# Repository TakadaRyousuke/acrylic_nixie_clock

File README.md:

# acrylic_nixie_clock
アクリル板を用いた疑似ニキシー時計のRepository。　回路データ、3DCADデータ、プログラムなど全部

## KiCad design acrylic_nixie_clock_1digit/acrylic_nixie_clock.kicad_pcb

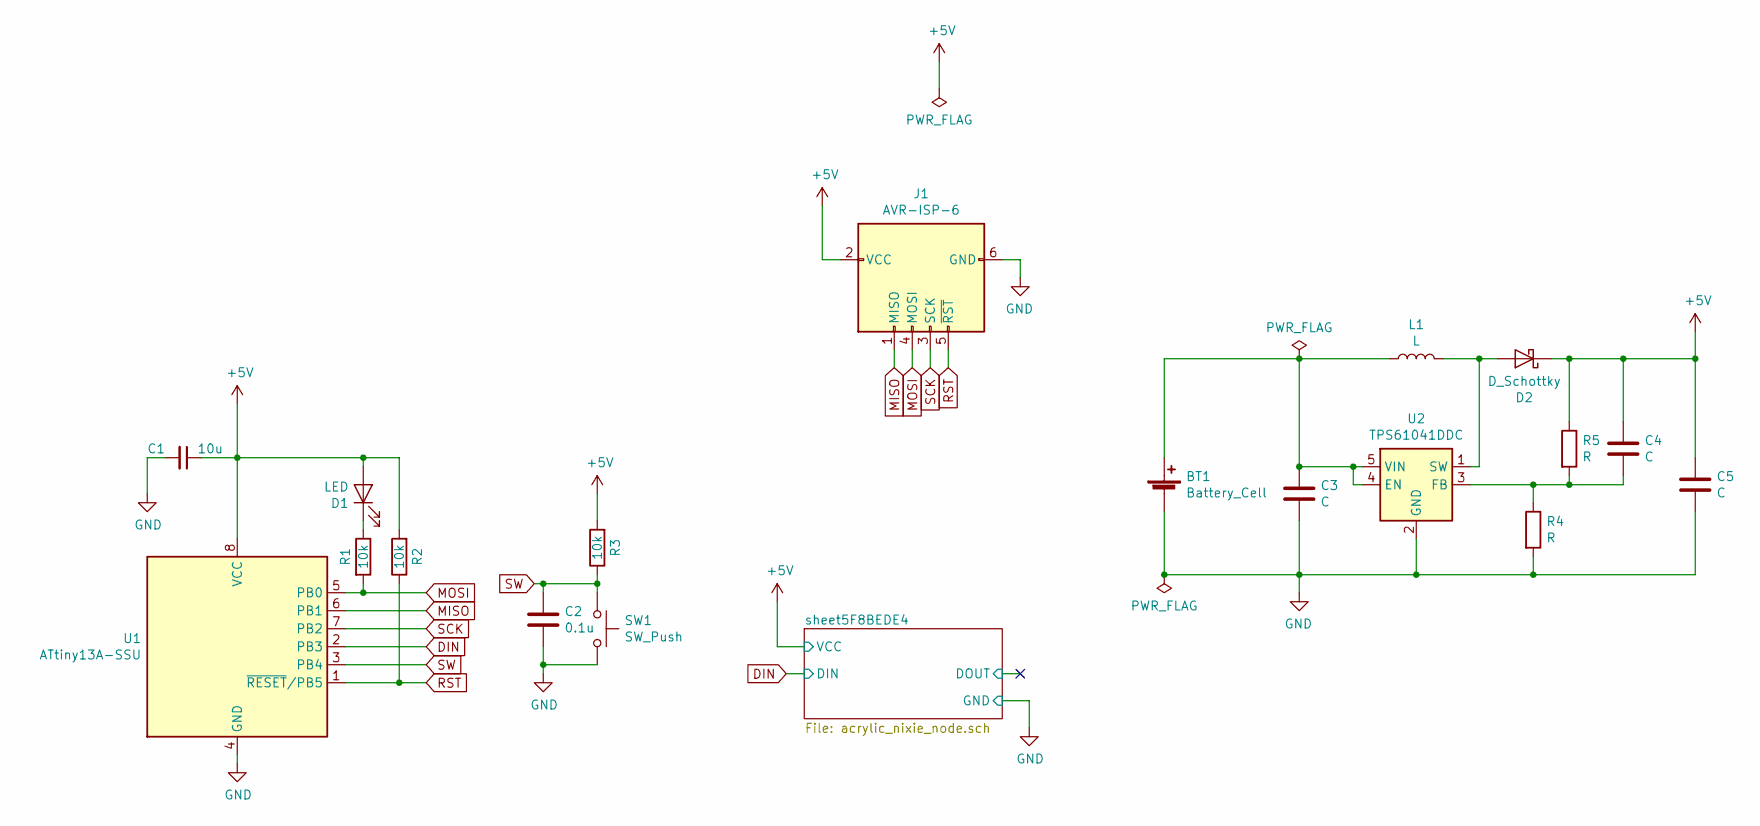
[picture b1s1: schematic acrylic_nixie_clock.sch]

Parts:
BT1: Battery_Cell; BatteryHolder_Keystone_1058_1x2032
C1: 10u; C_0603_1608Metric; LCSC C19702
C2: 0.1u; C_0603_1608Metric; LCSC C14858
C3, C4, C5: C; C_0603_1608Metric
D1: LED; LED_0603_1608Metric
D2: D_Schottky; D_SOD-123
J1: AVR-ISP-6; ISP-6
L1: L; L_0603_1608Metric
R1, R2, R3: 10k; R_0603_1608Metric_Pad1.05x0.95mm_HandSolder; LCSC C25804
R4, R5: R; R_0603_1608Metric_Pad1.05x0.95mm_HandSolder
SW1: SW_Push; SW_SPST_TL3342; LCSC C318884
U1: ATtiny13A-SSU; SOIC-8_3.9x4.9mm_P1.27mm
U2: TPS61041DDC; SOT-23-5

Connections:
+5V: C1.1, C4.1, C5.1, D1.2 (A), D2.1 (K), J1.2 (VCC), R2.2, R3.2, R5.1, U1.8 (VCC); also elsewhere on the board
DIN: U1.2 (PB3); also elsewhere on the board
GND: BT1.2 (-), C1.2, C2.2, C3.2, C5.2, J1.6 (GND), R4.2, SW1.2, U1.4 (GND), U2.2 (GND); also elsewhere on the board
MISO: J1.1 (MISO), U1.6 (PB1)
MOSI: J1.4 (MOSI), R1.2, U1.5 (PB0)
unnamed: BT1.1 (+), C3.1, L1.1, U2.4 (EN), U2.5 (VIN)
unnamed: C4.2, R4.1, R5.2, U2.3 (FB)
unnamed: D1.1 (K), R1.1
unnamed: D2.2 (A), L1.2, U2.1 (SW)
RST: J1.5 (~RST), R2.1, U1.1 (~RESET~/PB5)
SCK: J1.3 (SCK), U1.7 (PB2)
SW: C2.1, R3.1, SW1.1, U1.3 (PB4)

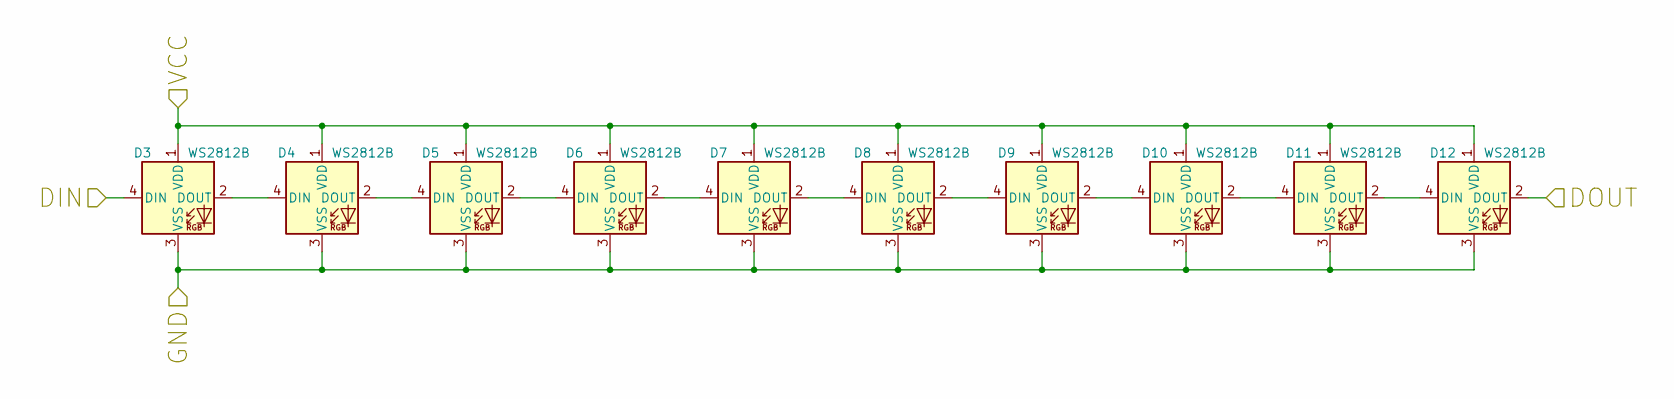
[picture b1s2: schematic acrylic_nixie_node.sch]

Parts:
D3, D4, D5, D6, D7, D8, D9, D10, D11, D12: WS2812B; LED_WS2812B_PLCC4_5.0x5.0mm_P3.2mm; LCSC C114586

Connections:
+5V: D3.1 (VDD), D4.1 (VDD), D5.1 (VDD), D6.1 (VDD), D7.1 (VDD), D8.1 (VDD), D9.1 (VDD), D10.1 (VDD), D11.1 (VDD), D12.1 (VDD); also elsewhere on the board
/sheet5F8BEDE4/DOUT: D12.2 (DOUT)
DIN: D3.4 (DIN); also elsewhere on the board
GND: D3.3 (VSS), D4.3 (VSS), D5.3 (VSS), D6.3 (VSS), D7.3 (VSS), D8.3 (VSS), D9.3 (VSS), D10.3 (VSS), D11.3 (VSS), D12.3 (VSS); also elsewhere on the board
unnamed: D3.2 (DOUT), D4.4 (DIN)
unnamed: D4.2 (DOUT), D5.4 (DIN)
unnamed: D5.2 (DOUT), D6.4 (DIN)
unnamed: D6.2 (DOUT), D7.4 (DIN)
unnamed: D7.2 (DOUT), D8.4 (DIN)
unnamed: D8.2 (DOUT), D9.4 (DIN)
unnamed: D10.2 (DOUT), D11.4 (DIN)
unnamed: D9.2 (DOUT), D10.4 (DIN)
unnamed: D11.2 (DOUT), D12.4 (DIN)

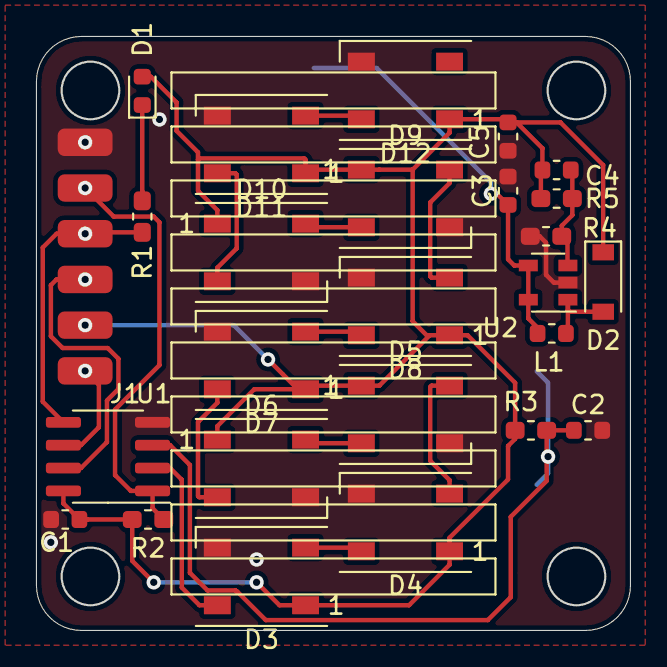
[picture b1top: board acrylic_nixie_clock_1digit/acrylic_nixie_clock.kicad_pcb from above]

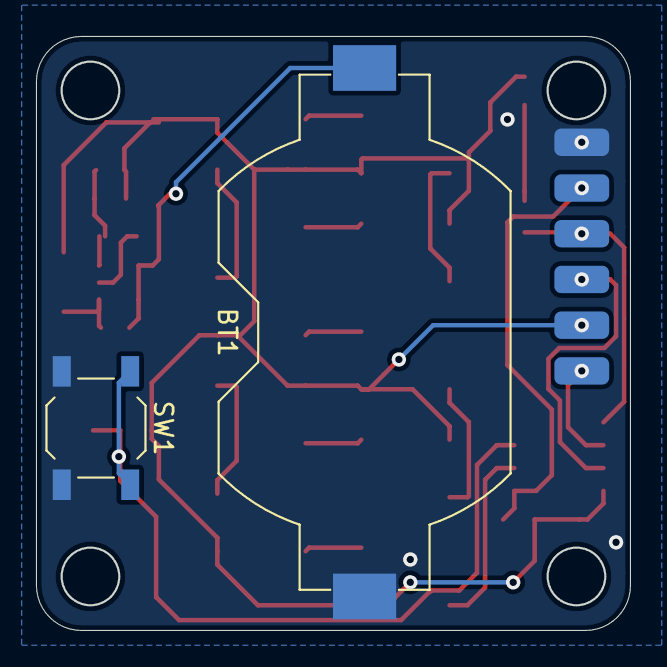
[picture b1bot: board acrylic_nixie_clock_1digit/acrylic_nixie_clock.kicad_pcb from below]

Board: 2 copper layers, 33.0 x 33.0 mm, 28 parts (2 on the bottom side), 21 nets.

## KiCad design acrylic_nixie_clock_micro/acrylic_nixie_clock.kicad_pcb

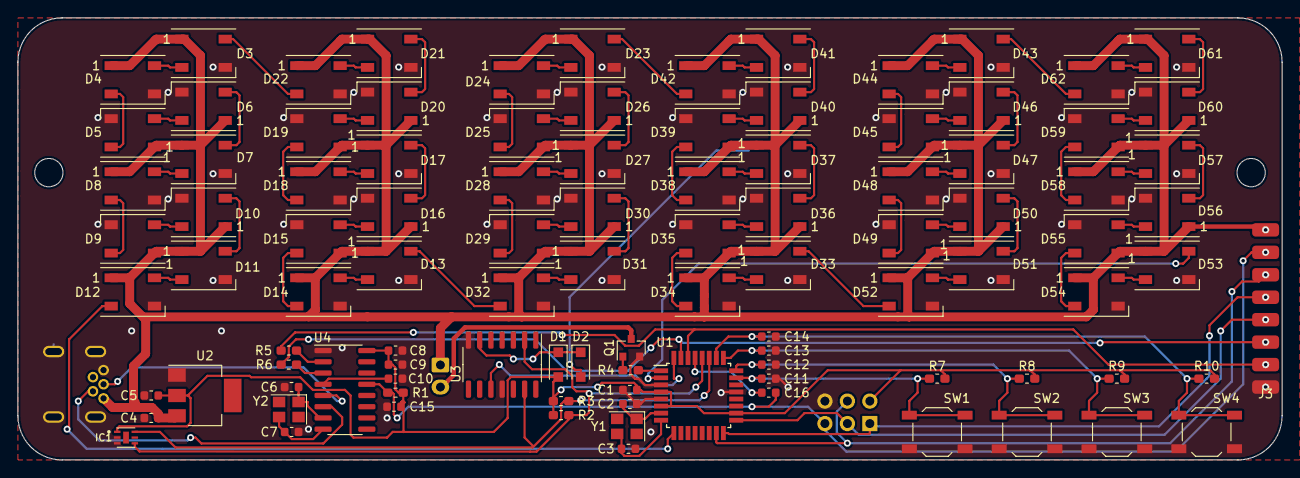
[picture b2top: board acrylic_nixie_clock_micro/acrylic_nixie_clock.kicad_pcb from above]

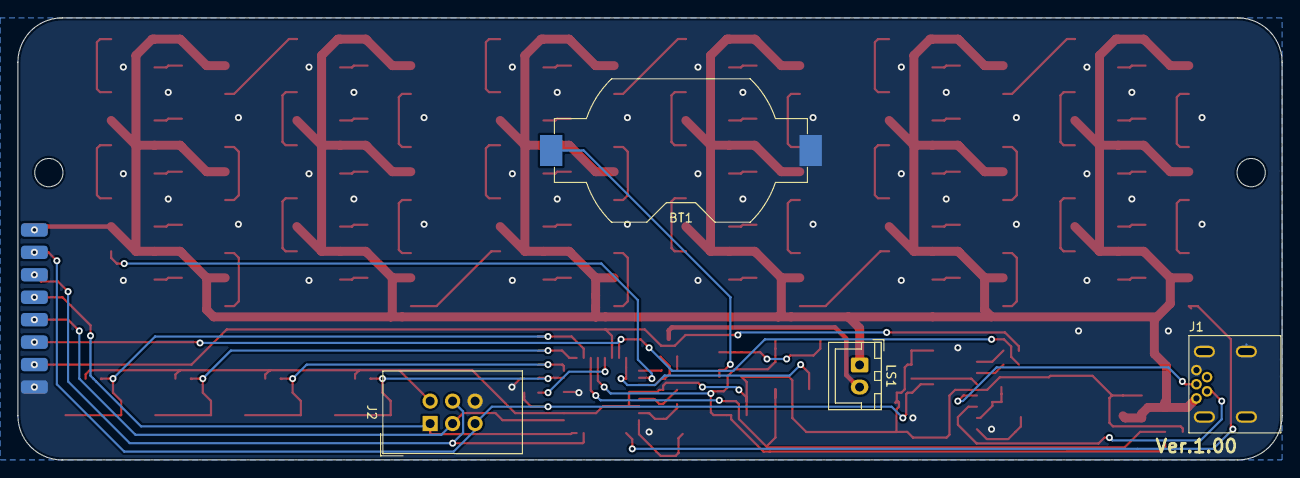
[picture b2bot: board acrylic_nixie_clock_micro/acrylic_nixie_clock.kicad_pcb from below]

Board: 2 copper layers, 143.0 x 50.0 mm, 105 parts (4 on the bottom side), 92 nets.

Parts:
BT1: Battery_Cell; BatteryHolder_Keystone_1058_1x2032
C1, C8: 10u; C_0603_1608Metric
C2, C3, C6, C7: 20p; C_0603_1608Metric
C4, C5, C11, C12, C13, C14, C15, C16: 0.1u; C_0603_1608Metric
C9: 100n; C_0603_1608Metric
C10: 1n; C_0603_1608Metric
D1, D2: B5819W; D_SOD-123F
D3, D4, D5, D6, D7, D8, D9, D10, D11, D12, D13, D14, D15, D16, D17, D18, D19, D20, D21, D22, D23, D24, D25, D26, D27, D28, D29, D30, D31, D32, D33, D34, D35, D36, D37, D38, D39, D40, D41, D42, D43, D44, D45, D46, D47, D48, D49, D50, D51, D52, D53, D54, D55, D56, D57, D58, D59, D60, D61, D62: WS2812B; LED_WS2812B_PLCC4_5.0x5.0mm_P3.2mm
IC1: OPT3001DNPR; SON65P200X200X65-7N
J1: USB_B_Micro; MUSB-5BF01ASMUSB-5BF01AS
J2: AVR-ISP-6; IDC-Header_2x03_P2.54mm_Vertical
J3: Conn_01x08_Female; writer_card
LS1: Speaker; JST_XH_B2B-XH-A_1x02_P2.50mm_Vertical
Q1: S9013; SOT-23
R1, R2, R3, R4, R7, R8, R9, R10: 10k; R_0603_1608Metric_Pad1.05x0.95mm_HandSolder
R5, R6: 1k; R_0603_1608Metric_Pad1.05x0.95mm_HandSolder
SW1, SW2, SW3, SW4: SW_Push; SW_SPST_TL3342
U1: ATmega328P-AU; TQFP-32_7x7mm_P0.8mm
U2: AMS1117-3.3v; SOT-223
U3: RX-8025T-UB; SOIC-14_3.9x8.7mm_P1.27mm
U4: CH340G; SOIC-16_3.9x9.9mm_P1.27mm
Y1: X322516MLB4SI; Crystal_SMD_3225-4Pin_3.2x2.5mm
Y2: 12MHZ; Crystal_SMD_3225-4Pin_3.2x2.5mm

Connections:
+3V3: C1.2, C5.1, C8.1, C9.1, C15.1, D1.2, IC1.1, J2.2, R1.1, R2.2, R3.1, R7.1, R8.1, R9.1, R10.1, U1.4, U1.6, U1.18, U2.2, U4.16
+5V: C4.1, D3.1, D4.1, D5.1, D6.1, D7.1, D8.1, D9.1, D10.1, D11.1, D12.1, D13.1, D14.1, D15.1, D16.1, D17.1, D18.1, D19.1, D20.1, D21.1, D22.1, D23.1, D24.1, D25.1, D26.1, D27.1, D28.1, D29.1, D30.1, D31.1, D32.1, D33.1, D34.1, D35.1, D36.1, D37.1, D38.1, D39.1, D40.1, D41.1, D42.1, D43.1, D44.1, D45.1, D46.1, D47.1, D48.1, D49.1, D50.1, D51.1, D52.1, D53.1, D54.1, D55.1, D56.1, D57.1, D58.1, D59.1, D60.1, D61.1, D62.1, J1.1, J3.8, LS1.1, U2.3
/Sheet5F5F34C2/D+: J1.3, U4.5
/Sheet5F5F34C2/D-: J1.2, U4.6
/Sheet5F60D2EA/sheet5F5DBF36/DIN: D43.4, D62.2
/Sheet5F60D2EA/sheet5F5DD25D/DIN: D33.4, D52.2
/Sheet5F60D2EA/sheet5F5DD785/DIN: D23.4, D42.2
/Sheet5F60D2EA/sheet5F5DDD7F/DIN: D13.4, D32.2
/Sheet5F60D2EA/sheet5F5DE4E8/DIN: D3.4, D22.2
DIN: D53.4, U1.2
DOUT: D12.2, U1.9
GND: BT1.2, C1.1, C2.1, C3.1, C4.2, C5.2, C6.2, C7.2, C8.2, C9.2, C10.2, C11.2, C12.2, C13.2, C14.2, C15.2, D3.3, D4.3, D5.3, D6.3, D7.3, D8.3, D9.3, D10.3, D11.3, D12.3, D13.3, D14.3, D15.3, D16.3, D17.3, D18.3, D19.3, D20.3, D21.3, D22.3, D23.3, D24.3, D25.3, D26.3, D27.3, D28.3, D29.3, D30.3, D31.3, D32.3, D33.3, D34.3, D35.3, D36.3, D37.3, D38.3, D39.3, D40.3, D41.3, D42.3, D43.3, D44.3, D45.3, D46.3, D47.3, D48.3, D49.3, D50.3, D51.3, D52.3, D53.3, D54.3, D55.3, D56.3, D57.3, D58.3, D59.3, D60.3, D61.3, D62.3, IC1.2, IC1.3, J1.5, J2.6, J3.1, Q1.2, SW1.2, SW2.2, SW3.2, SW4.2, U1.3, U1.5, U1.21, U2.1, U3.7, U3.11, U4.1
INT: U1.32, U3.10
MISO: J2.1, J3.5, U1.16
MOSI: J2.4, J3.6, U1.15
unnamed: BT1.1, D2.2
unnamed: C2.2, U1.7, Y1.1
unnamed: C3.2, U1.8, Y1.3
unnamed: C6.1, U4.7, Y2.1
unnamed: C7.1, U4.8, Y2.3
unnamed: C10.1, U4.4
unnamed: C16.2, U1.29
unnamed: D1.1, D2.1, U3.6
unnamed: D3.2, D4.4
unnamed: D4.2, D5.4
unnamed: D5.2, D6.4
unnamed: D6.2, D7.4
unnamed: D7.2, D8.4
unnamed: D8.2, D9.4
unnamed: D10.2, D11.4
unnamed: D9.2, D10.4
unnamed: D11.2, D12.4
unnamed: D13.2, D14.4
unnamed: D14.2, D15.4
unnamed: D15.2, D16.4
unnamed: D16.2, D17.4
unnamed: D17.2, D18.4
unnamed: D18.2, D19.4
unnamed: D19.2, D20.4
unnamed: D20.2, D21.4
unnamed: D21.2, D22.4
unnamed: D23.2, D24.4
unnamed: D24.2, D25.4
unnamed: D25.2, D26.4
unnamed: D26.2, D27.4
unnamed: D27.2, D28.4
unnamed: D28.2, D29.4
unnamed: D29.2, D30.4
unnamed: D30.2, D31.4
unnamed: D31.2, D32.4
unnamed: D33.2, D34.4
unnamed: D34.2, D35.4
unnamed: D35.2, D36.4
unnamed: D36.2, D37.4
unnamed: D37.2, D38.4
unnamed: D38.2, D39.4
unnamed: D39.2, D40.4
unnamed: D40.2, D41.4
unnamed: D41.2, D42.4
unnamed: D43.2, D44.4
unnamed: D44.2, D45.4
unnamed: D45.2, D46.4
unnamed: D46.2, D47.4
unnamed: D47.2, D48.4
unnamed: D48.2, D49.4
unnamed: D49.2, D50.4
unnamed: D50.2, D51.4
unnamed: D51.2, D52.4
unnamed: D53.2, D54.4
unnamed: D54.2, D55.4
unnamed: D55.2, D56.4
unnamed: D56.2, D57.4
unnamed: D57.2, D58.4
unnamed: D58.2, D59.4
unnamed: D59.2, D60.4
unnamed: D60.2, D61.4
unnamed: D61.2, D62.4
unnamed: LS1.2, Q1.3
unnamed: Q1.1, R4.2
unnamed: R5.1, U4.2
unnamed: R6.1, U4.3
RST: C16.1, J2.5, J3.7, R1.2, U4.13
RXD: J3.2, R5.2, U1.30
SCK: J2.3, J3.4, U1.17
SCL: IC1.4, R2.1, U1.28, U3.2
SDA: IC1.6, R3.2, U1.27, U3.13
SPK: R4.1, U1.1
SW1: C11.1, R7.2, SW1.1, U1.23
SW2: C12.1, R8.2, SW2.1, U1.24
SW3: C13.1, R9.2, SW3.1, U1.25
SW4: C14.1, R10.2, SW4.1, U1.26
TXD: J3.3, R6.2, U1.31

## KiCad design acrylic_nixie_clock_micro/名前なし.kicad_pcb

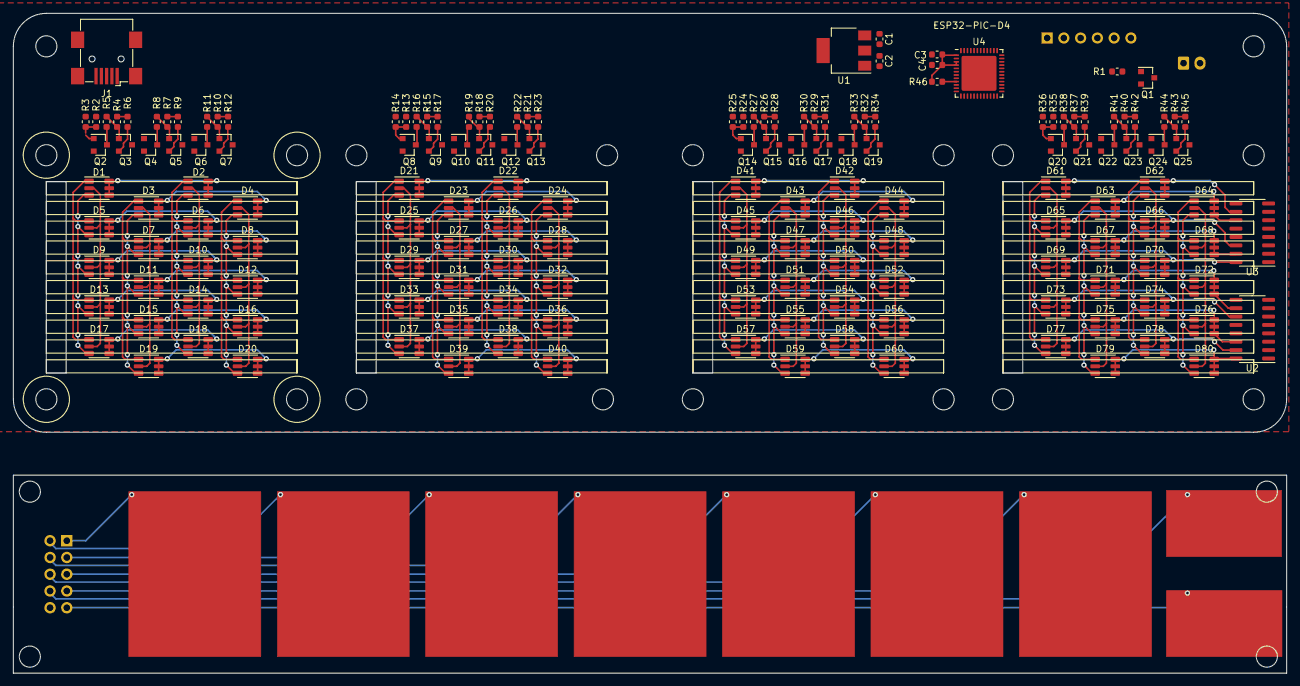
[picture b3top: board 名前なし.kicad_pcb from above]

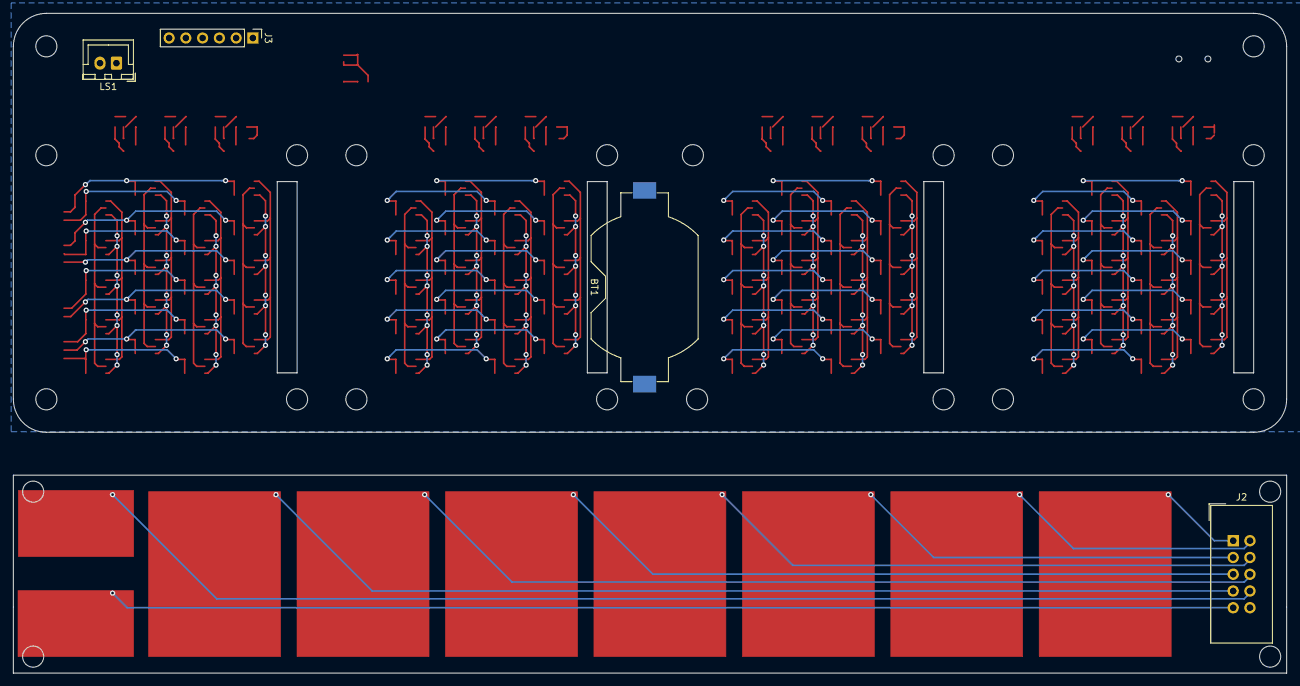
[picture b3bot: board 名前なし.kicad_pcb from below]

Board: 2 copper layers, 193.0 x 63.5 mm, 164 parts (4 on the bottom side), 89 nets.

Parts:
BT1: Battery_Cell; BatteryHolder_Keystone_1058_1x2032
C1: 0.1u; C_0603_1608Metric
C2: 1u; C_0603_1608Metric
C3: 0.1uF; C_0603_1608Metric
C4: 10uF; C_0603_1608Metric
D1, D2, D3, D4, D5, D6, D7, D8, D9, D10, D11, D12, D13, D14, D15, D16, D17, D18, D19, D20, D21, D22, D23, D24, D25, D26, D27, D28, D29, D30, D31, D32, D33, D34, D35, D36, D37, D38, D39, D40, D41, D42, D43, D44, D45, D46, D47, D48, D49, D50, D51, D52, D53, D54, D55, D56, D57, D58, D59, D60, D61, D62, D63, D64, D65, D66, D67, D68, D69, D70, D71, D72, D73, D74, D75, D76, D77, D78, D79, D80: FM-Z3535RGBA-SH; LED_ROHM_SMLVN6
J1: USB_B_Micro; USB_Mini-B_Wuerth_65100516121_Horizontal
J2: Conn_02x05_Odd_Even; IDC-Header_2x05_P2.54mm_Vertical
J3: Conn_01x06_Female; PinHeader_1x06_P2.54mm_Vertical
LS1: Speaker; JST_XH_B2B-XH-A_1x02_P2.50mm_Vertical
Q1, Q2, Q4, Q6, Q8, Q10, Q12, Q14, Q16, Q18, Q20, Q22, Q24: S9013; SOT-23
Q3, Q5, Q7, Q9, Q11, Q13, Q15, Q17, Q19, Q21, Q23, Q25: SS8550; SOT-23
R1, R2, R4, R5, R7, R8, R10, R11, R13, R15, R16, R18, R19, R21, R22, R24, R26, R27, R29, R30, R32, R33, R35, R37, R38, R40, R41, R43, R44, R46: 10k; R_0603_1608Metric
R3, R14, R25, R36: 1k; R_0603_1608Metric
R6, R9, R12, R17, R20, R23, R28, R31, R34, R39, R42, R45: 500; R_0603_1608Metric
U1: LT1083-3.3; SOT-223
U2, U3: ULN2003ADR; SOIC-16_3.9x9.9mm_P1.27mm
U4: ESP32-PICO-D4; QFN-48-1EP_7x7mm_P0.5mm_EP5.3x5.3mm

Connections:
+3V3: C2.1, C3.1, C4.1, J3.3, R46.1, U1.2, U4.1, U4.3, U4.4, U4.37, U4.43, U4.46
+5V: C1.1, J1.1, LS1.1, R4.1, R6.1, R7.1, R9.1, R10.1, R12.1, R15.1, R17.1, R18.1, R20.1, R21.1, R23.1, R26.1, R28.1, R29.1, R31.1, R32.1, R34.1, R37.1, R39.1, R40.1, R42.1, R43.1, R45.1, U1.3
/Sheet5F60D2EA/sheet5F60EC1D/K0: D19.4, D19.5, D19.6, D20.4, D20.5, D20.6, D39.4, D39.5, D39.6, D40.4, D40.5, D40.6, D59.4, D59.5, D59.6, D60.4, D60.5, D60.6, D79.4, D79.5, D79.6, D80.4, D80.5, D80.6, U2.16
/Sheet5F60D2EA/sheet5F60EC1D/K1: D17.4, D17.5, D17.6, D18.4, D18.5, D18.6, D37.4, D37.5, D37.6, D38.4, D38.5, D38.6, D57.4, D57.5, D57.6, D58.4, D58.5, D58.6, D77.4, D77.5, D77.6, D78.4, D78.5, D78.6, U2.15
/Sheet5F60D2EA/sheet5F60EC1D/K2: D15.4, D15.5, D15.6, D16.4, D16.5, D16.6, D35.4, D35.5, D35.6, D36.4, D36.5, D36.6, D55.4, D55.5, D55.6, D56.4, D56.5, D56.6, D75.4, D75.5, D75.6, D76.4, D76.5, D76.6, U2.14
/Sheet5F60D2EA/sheet5F60EC1D/K3: D13.4, D13.5, D13.6, D14.4, D14.5, D14.6, D33.4, D33.5, D33.6, D34.4, D34.5, D34.6, D53.4, D53.5, D53.6, D54.4, D54.5, D54.6, D73.4, D73.5, D73.6, D74.4, D74.5, D74.6, U2.11
/Sheet5F60D2EA/sheet5F60EC1D/K4: D11.4, D11.5, D11.6, D12.4, D12.5, D12.6, D31.4, D31.5, D31.6, D32.4, D32.5, D32.6, D51.4, D51.5, D51.6, D52.4, D52.5, D52.6, D71.4, D71.5, D71.6, D72.4, D72.5, D72.6, U2.10
/Sheet5F60D2EA/sheet5F60EC1D/K5: D9.4, D9.5, D9.6, D10.4, D10.5, D10.6, D29.4, D29.5, D29.6, D30.4, D30.5, D30.6, D49.4, D49.5, D49.6, D50.4, D50.5, D50.6, D69.4, D69.5, D69.6, D70.4, D70.5, D70.6, U3.16
/Sheet5F60D2EA/sheet5F60EC1D/K6: D7.4, D7.5, D7.6, D8.4, D8.5, D8.6, D27.4, D27.5, D27.6, D28.4, D28.5, D28.6, D47.4, D47.5, D47.6, D48.4, D48.5, D48.6, D67.4, D67.5, D67.6, D68.4, D68.5, D68.6, U3.15
/Sheet5F60D2EA/sheet5F60EC1D/K7: D5.4, D5.5, D5.6, D6.4, D6.5, D6.6, D25.4, D25.5, D25.6, D26.4, D26.5, D26.6, D45.4, D45.5, D45.6, D46.4, D46.5, D46.6, D65.4, D65.5, D65.6, D66.4, D66.5, D66.6, U3.14
/Sheet5F60D2EA/sheet5F60EC1D/K8: D3.4, D3.5, D3.6, D4.4, D4.5, D4.6, D23.4, D23.5, D23.6, D24.4, D24.5, D24.6, D43.4, D43.5, D43.6, D44.4, D44.5, D44.6, D63.4, D63.5, D63.6, D64.4, D64.5, D64.6, U3.11
/Sheet5F60D2EA/sheet5F60EC1D/K9: D1.4, D1.5, D1.6, D2.4, D2.5, D2.6, D21.4, D21.5, D21.6, D22.4, D22.5, D22.6, D41.4, D41.5, D41.6, D42.4, D42.5, D42.6, D61.4, D61.5, D61.6, D62.4, D62.5, D62.6, U3.10
/Sheet5F60D2EA/sheet5F60EC1D/LED_RGB/B: D1.3, D2.3, D3.3, D4.3, D5.3, D6.3, D7.3, D8.3, D9.3, D10.3, D11.3, D12.3, D13.3, D14.3, D15.3, D16.3, D17.3, D18.3, D19.3, D20.3, Q3.3
/Sheet5F60D2EA/sheet5F60EC1D/LED_RGB/G: D1.1, D2.1, D3.1, D4.1, D5.1, D6.1, D7.1, D8.1, D9.1, D10.1, D11.1, D12.1, D13.1, D14.1, D15.1, D16.1, D17.1, D18.1, D19.1, D20.1, Q5.3
/Sheet5F60D2EA/sheet5F60EC1D/LED_RGB/R: D1.2, D2.2, D3.2, D4.2, D5.2, D6.2, D7.2, D8.2, D9.2, D10.2, D11.2, D12.2, D13.2, D14.2, D15.2, D16.2, D17.2, D18.2, D19.2, D20.2, Q7.3
/Sheet5F60D2EA/sheet5F76DABD/LED_RGB/B: D21.3, D22.3, D23.3, D24.3, D25.3, D26.3, D27.3, D28.3, D29.3, D30.3, D31.3, D32.3, D33.3, D34.3, D35.3, D36.3, D37.3, D38.3, D39.3, D40.3, Q9.3
/Sheet5F60D2EA/sheet5F76DABD/LED_RGB/G: D21.1, D22.1, D23.1, D24.1, D25.1, D26.1, D27.1, D28.1, D29.1, D30.1, D31.1, D32.1, D33.1, D34.1, D35.1, D36.1, D37.1, D38.1, D39.1, D40.1, Q11.3
/Sheet5F60D2EA/sheet5F76DABD/LED_RGB/R: D21.2, D22.2, D23.2, D24.2, D25.2, D26.2, D27.2, D28.2, D29.2, D30.2, D31.2, D32.2, D33.2, D34.2, D35.2, D36.2, D37.2, D38.2, D39.2, D40.2, Q13.3
/Sheet5F60D2EA/sheet5F771B13/LED_RGB/B: D41.3, D42.3, D43.3, D44.3, D45.3, D46.3, D47.3, D48.3, D49.3, D50.3, D51.3, D52.3, D53.3, D54.3, D55.3, D56.3, D57.3, D58.3, D59.3, D60.3, Q15.3
/Sheet5F60D2EA/sheet5F771B13/LED_RGB/G: D41.1, D42.1, D43.1, D44.1, D45.1, D46.1, D47.1, D48.1, D49.1, D50.1, D51.1, D52.1, D53.1, D54.1, D55.1, D56.1, D57.1, D58.1, D59.1, D60.1, Q17.3
/Sheet5F60D2EA/sheet5F771B13/LED_RGB/R: D41.2, D42.2, D43.2, D44.2, D45.2, D46.2, D47.2, D48.2, D49.2, D50.2, D51.2, D52.2, D53.2, D54.2, D55.2, D56.2, D57.2, D58.2, D59.2, D60.2, Q19.3
/Sheet5F60D2EA/sheet5F775B37/LED_RGB/B: D61.3, D62.3, D63.3, D64.3, D65.3, D66.3, D67.3, D68.3, D69.3, D70.3, D71.3, D72.3, D73.3, D74.3, D75.3, D76.3, D77.3, D78.3, D79.3, D80.3, Q21.3
/Sheet5F60D2EA/sheet5F775B37/LED_RGB/G: D61.1, D62.1, D63.1, D64.1, D65.1, D66.1, D67.1, D68.1, D69.1, D70.1, D71.1, D72.1, D73.1, D74.1, D75.1, D76.1, D77.1, D78.1, D79.1, D80.1, Q23.3
/Sheet5F60D2EA/sheet5F775B37/LED_RGB/R: D61.2, D62.2, D63.2, D64.2, D65.2, D66.2, D67.2, D68.2, D69.2, D70.2, D71.2, D72.2, D73.2, D74.2, D75.2, D76.2, D77.2, D78.2, D79.2, D80.2, Q25.3
B: Q2.2, Q8.2, Q14.2, Q20.2, U4.33
DTR: J3.6, R46.2, U4.9
EN1: R2.2, U4.29
EN2: R13.2, U4.28
EN3: R24.2, U4.27
EN4: R35.2, U4.25
G: Q4.2, Q10.2, Q16.2, Q22.2, U4.31
GND: BT1.2, C1.2, C2.2, C3.2, C4.2, J1.5, J3.1, Q1.2, R3.1, R14.1, R25.1, R36.1, U1.1, U2.8, U2.9, U3.8, U3.9, U4.49
K0: U2.1, U4.13
K1: U2.2, U4.14
K2: U2.3, U4.15
K3: U2.6, U4.16
K4: U2.7, U4.17
K5: U3.1, U4.18
K6: U3.2, U4.20
K7: U3.3, U4.21
K8: U3.6, U4.22
K9: U3.7, U4.23
unnamed: BT1.1, U4.19
unnamed: LS1.2, Q1.3
unnamed: Q1.1, R1.2
unnamed: Q2.1, Q4.1, Q6.1, R2.1, R3.2
unnamed: Q2.3, R5.1
unnamed: Q3.1, R4.2, R5.2
unnamed: Q3.2, R6.2
unnamed: Q4.3, R8.1
unnamed: Q5.1, R7.2, R8.2
unnamed: Q5.2, R9.2
unnamed: Q6.3, R11.1
unnamed: Q7.1, R10.2, R11.2
unnamed: Q7.2, R12.2
unnamed: Q8.3, R16.1
unnamed: Q9.1, R15.2, R16.2
unnamed: Q9.2, R17.2
unnamed: Q8.1, Q10.1, Q12.1, R13.1, R14.2
unnamed: Q10.3, R19.1
unnamed: Q11.1, R18.2, R19.2
unnamed: Q11.2, R20.2
unnamed: Q12.3, R22.1
unnamed: Q13.1, R21.2, R22.2
unnamed: Q13.2, R23.2
unnamed: Q14.1, Q16.1, Q18.1, R24.1, R25.2
unnamed: Q14.3, R27.1
unnamed: Q15.1, R26.2, R27.2
unnamed: Q15.2, R28.2
unnamed: Q16.3, R30.1
unnamed: Q17.1, R29.2, R30.2
unnamed: Q17.2, R31.2
unnamed: Q18.3, R33.1
unnamed: Q19.1, R32.2, R33.2
unnamed: Q19.2, R34.2
unnamed: Q20.1, Q22.1, Q24.1, R35.1, R36.2
unnamed: Q20.3, R38.1
unnamed: Q21.1, R37.2, R38.2
unnamed: Q21.2, R39.2
unnamed: Q22.3, R41.1
unnamed: Q23.1, R40.2, R41.2
unnamed: Q23.2, R42.2
unnamed: Q24.3, R44.1
unnamed: Q25.1, R43.2, R44.2
unnamed: Q25.2, R45.2
R: Q6.2, Q12.2, Q18.2, Q24.2, U4.30
RXD: J3.4, U4.40
SPK: R1.1, U4.32
TXD: J3.5, U4.41

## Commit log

2020-10-09 Lixie6digit's circuit is complated.
    Lixie6digit's circuit is complated.
2020-10-09 1桁キーホルダーの回路図の1st commit
    1桁キーホルダーの回路図の1st commit
2020-10-12 問題点を修正
    CH304Gの電源電圧を3.3Vに
    RSTにコンデンサを追加
    USBのフットプリントを修正
    カードコネクタの追加
